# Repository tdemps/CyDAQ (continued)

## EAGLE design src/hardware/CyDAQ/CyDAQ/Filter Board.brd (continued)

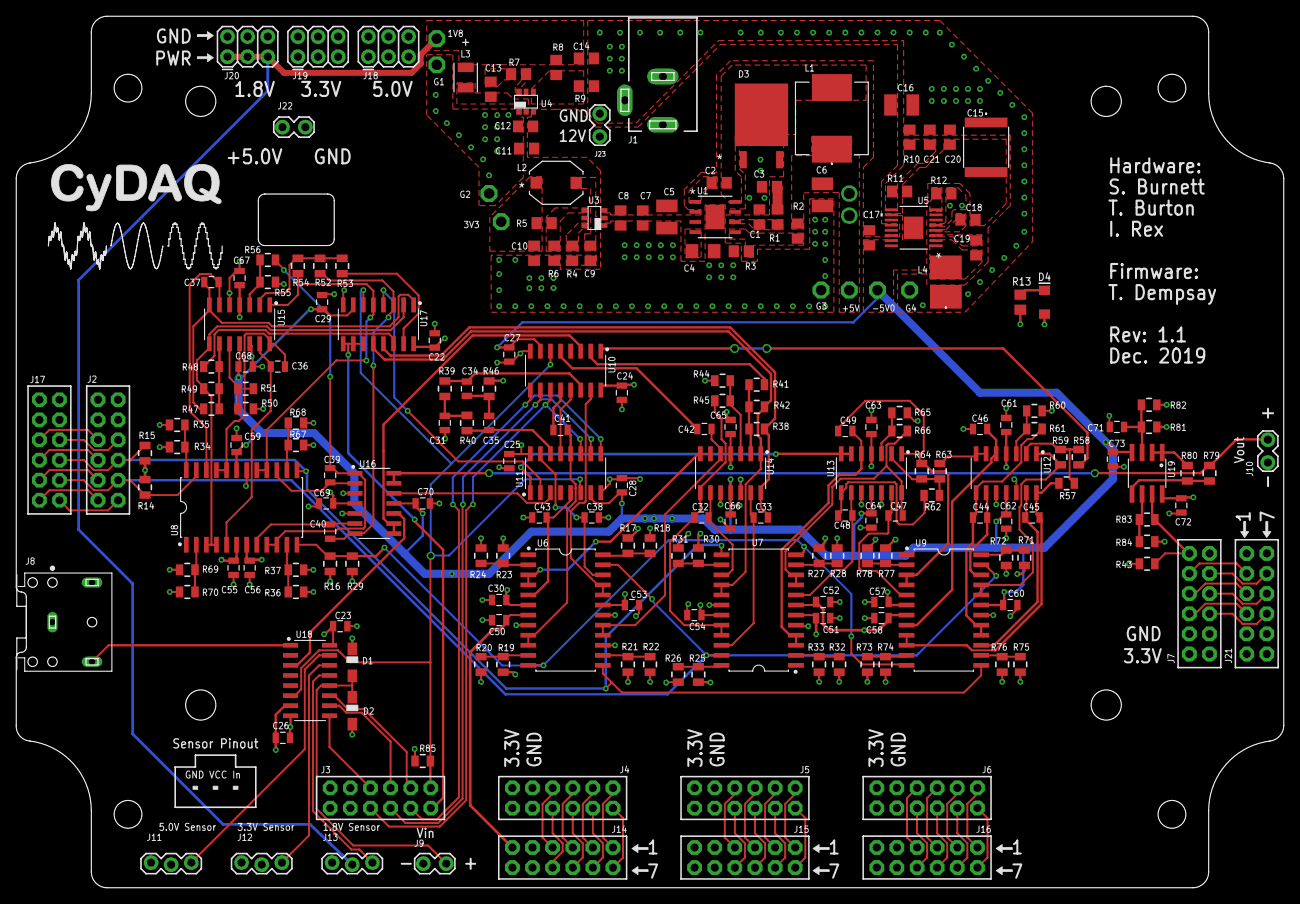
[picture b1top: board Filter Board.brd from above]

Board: 4 copper layers, 160.0 x 110.0 mm, 215 parts (0 on the bottom side), 160 nets.

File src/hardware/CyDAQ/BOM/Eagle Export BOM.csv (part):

"Part";"Value";"Device";"Package";"Description";"AVAILABILITY";"BOM";"CUI_PURCHASE_URL";"DESCRIPTION";"MANUFACTURER_PART_NUMBER";"MF";"MP";"MPN";"OC_FARNELL";"OC_NEWARK";"PACKAGE";"POPULARITY";"PRICE";"PROD_ID";"SPICEPREFIX";"TP_SIGNAL_NAME";"URL";"VALUE";"VENDOR";
"+5V";"TPPAD1-13";"TPPAD1-13";"P1-13";"Test pad";"";"";"";"";"";"";"";"";"";"";"";"12";"";"";"";"";"";"";"";
"-5V";"TPPAD1-13";"TPPAD1-13";"P1-13";"Test pad";"";"";"";"";"";"";"";"";"";"";"";"12";"";"";"";"";"";"";"";
"1V8";"TPPAD1-13";"TPPAD1-13";"P1-13";"Test pad";"";"";"";"";"";"";"";"";"";"";"";"12";"";"";"";"";"";"";"";
"3V3";"TPPAD1-13";"TPPAD1-13";"P1-13";"Test pad";"";"";"";"";"";"";"";"";"";"";"";"12";"";"";"";"";"";"";"";
"C1";"10pF";"C-USC0805";"C0805";"CAPACITOR, American symbol";"";"";"";"";"";"";"";"";"";"";"";"63";"";"";"C";"";"";"";"";
"C2";"100nF";"C-USC0805";"C0805";"CAPACITOR, American symbol";"";"";"";"";"";"";"";"";"";"";"";"63";"";"";"C";"";"";"";"";
"C3";"1.2nF";"C-USC0805";"C0805";"CAPACITOR, American symbol";"";"";"";"";"";"";"";"";"";"";"";"63";"";"";"C";"";"";"";"";
"C4";"8.2nF";"C-USC1206";"C1206";"CAPACITOR, American symbol";"";"";"";"";"";"";"";"";"";"";"";"24";"";"";"C";"";"";"";"";
"C5";"10uF";"C-USC1210";"C1210";"CAPACITOR, American symbol";"";"";"";"";"";"";"";"";"";"";"";"6";"";"";"C";"";"";"";"";
"C6";"47uF";"C-USC1210";"C1210";"CAPACITOR, American symbol";"";"";"";"";"";"";"";"";"";"";"";"6";"";"";"C";"";"";"";"";
"C7";"10uF";"C-USC0805";"C0805";"CAPACITOR, American symbol";"";"";"";"";"";"";"";"";"";"";"";"63";"";"";"C";"";"";"";"";
"C8";"100nF";"C-USC0805";"C0805";"CAPACITOR, American symbol";"";"";"";"";"";"";"";"";"";"";"";"63";"";"";"C";"";"";"";"";
"C9";"100nF";"C-USC0805";"C0805";"CAPACITOR, American symbol";"";"";"";"";"";"";"";"";"";"";"";"63";"";"";"C";"";"";"";"";
"C10";"22uF";"C-USC0805";"C0805";"CAPACITOR, American symbol";"";"";"";"";"";"";"";"";"";"";"";"63";"";"";"C";"";"";"";"";
"C11";"10uF";"C-USC0805";"C0805";"CAPACITOR, American symbol";"";"";"";"";"";"";"";"";"";"";"";"63";"";"";"C";"";"";"";"";
"C12";"100nF";"C-USC0805";"C0805";"CAPACITOR, American symbol";"";"";"";"";"";"";"";"";"";"";"";"63";"";"";"C";"";"";"";"";
"C13";"100nF";"C-USC0805";"C0805";"CAPACITOR, American symbol";"";"";"";"";"";"";"";"";"";"";"";"63";"";"";"C";"";"";"";"";
"C14";"22uF";"C-USC0805";"C0805";"CAPACITOR, American symbol";"";"";"";"";"";"";"";"";"";"";"";"63";"";"";"C";"";"";"";"";
"C15";"47uF";"CGA9N3X7R1_CGA9N3X7R1C476M230KB";"CGA9N3X7R1_CAP_5750";"";"";"";"";"";"CGA9N3X7R1C476M230KB";"";"";"";"";"";"";"";"";"";"";"";"";"";"TDK";
"C16";"22uF";"C-USC1210";"C1210";"CAPACITOR, American symbol";"";"";"";"";"";"";"";"";"";"";"";"6";"";"";"C";"";"";"";"";
"C17";"4.7uF";"C-USC0805";"C0805";"CAPACITOR, American symbol";"";"";"";"";"";"";"";"";"";"";"";"63";"";"";"C";"";"";"";"";
"C18";"2.2uF";"C-USC0805";"C0805";"CAPACITOR, American symbol";"";"";"";"";"";"";"";"";"";"";"";"63";"";"";"C";"";"";"";"";
"C19";"";"C-USC0805";"C0805";"CAPACITOR, American symbol";"";"";"";"";"";"";"";"";"";"";"";"63";"";"";"C";"";"";"";"";
"C20";"4.7uF";"C-USC0805";"C0805";"CAPACITOR, American symbol";"";"";"";"";"";"";"";"";"";"";"";"63";"";"";"C";"";"";"";"";
"C21";"33pF";"C-USC0805";"C0805";"CAPACITOR, American symbol";"";"";"";"";"";"";"";"";"";"";"";"63";"";"";"C";"";"";"";"";
"C22";"0.1uF";"NON_POL_0805/2012";"0805_H0.75";"";"";"";"";"";"";"";"";"";"";"";"";"";"";"";"";"";"";"";"";
"C23";"0.1uF";"NON_POL_0805/2012";"0805_H0.75";"";"";"";"";"";"";"";"";"";"";"";"";"";"";"";"";"";"";"";"";
"C24";"0.1uF";"NON_POL_0805/2012";"0805_H0.75";"";"";"";"";"";"";"";"";"";"";"";"";"";"";"";"";"";"";"";"";
"C25";"0.1uF";"NON_POL_0805/2012";"0805_H0.75";"";"";"";"";"";"";"";"";"";"";"";"";"";"";"";"";"";"";"";"";
"C26";"0.1uF";"NON_POL_0805/2012";"0805_H0.75";"";"";"";"";"";"";"";"";"";"";"";"";"";"";"";"";"";"";"";"";
"C27";"0.1uF";"NON_POL_0805/2012";"0805_H0.75";"";"";"";"";"";"";"";"";"";"";"";"";"";"";"";"";"";"";"";"";
"C28";"0.1uF";"NON_POL_0805/2012";"0805_H0.75";"";"";"";"";"";"";"";"";"";"";"";"";"";"";"";"";"";"";"";"";
"C29";"0.1uF";"NON_POL_0805/2012";"0805_H0.75";"";"";"";"";"";"";"";"";"";"";"";"";"";"";"";"";"";"";"";"";
"C30";"0.1uF";"NON_POL_0805/2012";"0805_H0.75";"";"";"";"";"";"";"";"";"";"";"";"";"";"";"";"";"";"";"";"";
"C31";"10uF";"NON_POL_0805/2012";"0805_H0.75";"";"";"";"";"";"";"";"";"";"";"";"";"";"";"";"";"";"";"";"";
"C32";"10nF";"NON_POL_0805/2012";"0805_H0.75";"";"";"";"";"";"";"";"";"";"";"";"";"";"";"";"";"";"";"";"";
"C33";"10nF";"NON_POL_0805/2012";"0805_H0.75";"";"";"";"";"";"";"";"";"";"";"";"";"";"";"";"";"";"";"";"";
"C34";"5.6uF";"NON_POL_0805/2012";"0805_H0.75";"";"";"";"";"";"";"";"";"";"";"";"";"";"";"";"";"";"";"";"";
"C35";"5.6uF";"NON_POL_0805/2012";"0805_H0.75";"";"";"";"";"";"";"";"";"";"";"";"";"";"";"";"";"";"";"";"";
"C36";"10nF";"NON_POL_0805/2012";"0805_H0.75";"";"";"";"";"";"";"";"";"";"";"";"";"";"";"";"";"";"";"";"";
"C37";"10nF";"NON_POL_0805/2012";"0805_H0.75";"";"";"";"";"";"";"";"";"";"";"";"";"";"";"";"";"";"";"";"";
"C38";"10nF";"NON_POL_0805/2012";"0805_H0.75";"";"";"";"";"";"";"";"";"";"";"";"";"";"";"";"";"";"";"";"";
"C39";"10nF";"NON_POL_0805/2012";"0805_H0.75";"";"";"";"";"";"";"";"";"";"";"";"";"";"";"";"";"";"";"";"";
"C40";"10nF";"NON_POL_0805/2012";"0805_H0.75";"";"";"";"";"";"";"";"";"";"";"";"";"";"";"";"";"";"";"";"";
"C41";"10nF";"NON_POL_0805/2012";"0805_H0.75";"";"";"";"";"";"";"";"";"";"";"";"";"";"";"";"";"";"";"";"";
"C42";"10nF";"NON_POL_0805/2012";"0805_H0.75";"";"";"";"";"";"";"";"";"";"";"";"";"";"";"";"";"";"";"";"";
"C43";"10nF";"NON_POL_0805/2012";"0805_H0.75";"";"";"";"";"";"";"";"";"";"";"";"";"";"";"";"";"";"";"";"";
"C44";"10nF";"NON_POL_0805/2012";"0805_H0.75";"";"";"";"";"";"";"";"";"";"";"";"";"";"";"";"";"";"";"";"";
"C45";"10nF";"NON_POL_0805/2012";"0805_H0.75";"";"";"";"";"";"";"";"";"";"";"";"";"";"";"";"";"";"";"";"";
"C46";"10nF";"NON_POL_0805/2012";"0805_H0.75";"";"";"";"";"";"";"";"";"";"";"";"";"";"";"";"";"";"";"";"";
"C47";"10nF";"NON_POL_0805/2012";"0805_H0.75";"";"";"";"";"";"";"";"";"";"";"";"";"";"";"";"";"";"";"";"";
"C48";"10nF";"NON_POL_0805/2012";"0805_H0.75";"";"";"";"";"";"";"";"";"";"";"";"";"";"";"";"";"";"";"";"";
"C49";"10nF";"NON_POL_0805/2012";"0805_H0.75";"";"";"";"";"";"";"";"";"";"";"";"";"";"";"";"";"";"";"";"";
"C50";"0.1uF";"NON_POL_0805/2012";"0805_H0.75";"";"";"";"";"";"";"";"";"";"";"";"";"";"";"";"";"";"";"";"";
"C51";"0.1uF";"NON_POL_0805/2012";"0805_H0.75";"";"";"";"";"";"";"";"";"";"";"";"";"";"";"";"";"";"";"";"";
"C52";"0.1uF";"NON_POL_0805/2012";"0805_H0.75";"";"";"";"";"";"";"";"";"";"";"";"";"";"";"";"";"";"";"";"";
"C53";"0.1uF";"NON_POL_0805/2012";"0805_H0.75";"";"";"";"";"";"";"";"";"";"";"";"";"";"";"";"";"";"";"";"";
"C54";"0.1uF";"NON_POL_0805/2012";"0805_H0.75";"";"";"";"";"";"";"";"";"";"";"";"";"";"";"";"";"";"";"";"";
"C55";"0.1uF";"NON_POL_0805/2012";"0805_H0.75";"";"";"";"";"";"";"";"";"";"";"";"";"";"";"";"";"";"";"";"";
"C56";"0.1uF";"NON_POL_0805/2012";"0805_H0.75";"";"";"";"";"";"";"";"";"";"";"";"";"";"";"";"";"";"";"";"";
"C57";"0.1uF";"NON_POL_0805/2012";"0805_H0.75";"";"";"";"";"";"";"";"";"";"";"";"";"";"";"";"";"";"";"";"";
"C58";"0.1uF";"NON_POL_0805/2012";"0805_H0.75";"";"";"";"";"";"";"";"";"";"";"";"";"";"";"";"";"";"";"";"";
"C59";"0.1uF";"NON_POL_0805/2012";"0805_H0.75";"";"";"";"";"";"";"";"";"";"";"";"";"";"";"";"";"";"";"";"";
"C60";"0.1uF";"NON_POL_0805/2012";"0805_H0.75";"";"";"";"";"";"";"";"";"";"";"";"";"";"";"";"";"";"";"";"";
"C61";"0.1uF";"NON_POL_0805/2012";"0805_H0.75";"";"";"";"";"";"";"";"";"";"";"";"";"";"";"";"";"";"";"";"";
"C62";"0.1uF";"NON_POL_0805/2012";"0805_H0.75";"";"";"";"";"";"";"";"";"";"";"";"";"";"";"";"";"";"";"";"";
"C63";"0.1uF";"NON_POL_0805/2012";"0805_H0.75";"";"";"";"";"";"";"";"";"";"";"";"";"";"";"";"";"";"";"";"";
"C64";"0.1uF";"NON_POL_0805/2012";"0805_H0.75";"";"";"";"";"";"";"";"";"";"";"";"";"";"";"";"";"";"";"";"";
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
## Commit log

2019-10-30 -Initial commit with Zybo firmware, old design files, old labs, and misc documentation
    -All old source work on cyDAQ is under /Archive/
    -Documentation folder contains relevant lab files, datasheets, etc.
2019-10-30 Pushing to Hardware branch
2019-10-30 Added base CyDAQ Altium project
2019-10-31 Adding Documentation to lab dev branch
2019-10-31 Adding Fourier Matlab
2019-10-31 New answer key for Fourier Labs and First Draft of Fourier Lab
2019-11-01 -firmware branch
2019-11-01 Initial upload
2019-11-07 Simplified things and streamlined it with hints so students aren't as lost in the process.
2019-11-11 Edited the Fourier Lab.
2019-11-12 -Merged XADC and I2C work into full_firmware project
    -Fixed XADC interrupt function to only be called when sequence is finished
    -Tested XADC (very preliminary)
2019-11-15 Added EAGLE design files at start of routing stage
2019-11-15 Placed components and started routing
2019-11-18 Continued routing.
2019-11-19 -Added comm test to main (Loopback for host)
    -Added button GPIO access to design
    -More XADC testing
    -Changed default AUX14 setting to unipolar
2019-11-19 Adding HW Datasheets
2019-11-19 Finished routing BP filter
2019-11-19 Rearranged some components for clarity
2019-11-20 Continued routing ~ 80% done
2019-11-20 Added some more traces!
2019-11-20 Used Gateswap magic to clean up some routing
2019-11-20 -changes
2019-11-20 Finished routing main filter area
2019-11-21 Finished most routing. Need to do -5v rail
2019-11-21 Fixed PMOD location
2019-11-21 Finished routing and made mechanical adjustments
2019-11-22 Added LED and fixed mounting holes
2019-11-22 Cleaned up frames
2019-11-22 Changed backup files
2019-11-22 Added silkscreen
2019-11-22 Made some final adjustments and added production files
2019-11-22 Adding Sam's BOM
2019-11-23 Updated silkscreen and uploaded board layout PDF
2019-11-23 Uploaded searchable schematic PDFs
2019-11-26 Adjusted notch filter values and uploaded BOM
2019-12-02 Added latest BOM
2019-12-02 Added marked layout PDF
2019-12-02 Updated TODO
2019-12-03 -encapsuled all filter definitions in filter library
    -redesigned mux and filter libraries to use main filter enum
    -many other improvements
2019-12-04 Fixed output MUX mapping
2019-12-05 Started fixing pinout on MUXs
2019-12-05 Finished rerouting fixed pinout
2019-12-09 -Added filter test in main.c
    -Added blank fsbl project to create BOOT.BIN for sdcard
    -Moved X9258 address macros to filter.h
    -Corrected some mux configs
    -Revised mux_driver to use PLL GPIO block instead of PS object
    -Rerouted filter and mux select pins to JE for Zybo
2019-12-09 Fixed button filter select on filter test
2019-12-09 Adding Sam's redesgined PMICs
2019-12-10 Modified board outline and updated silkscreen
2019-12-10 -Started working on timer based xadc
    -Added button blocking function
2019-12-10 Front end 2.0 initial commit
2019-12-10 Fixed Zybo mounting hole location
2019-12-12 -And the lord said let there be comments
    -Removal of some dusty commented code
    -Moved some definitions to their appropiate header files
2019-12-13 -Added debug flag support to more print statements
    -Added ping command
    -Added fetch command
    -Reworked sampling loop to decrease instructions between sample checks (less dropped samples)
    -Increased sample buffer size to 3000000
2019-12-16 -Changes to test program
2019-12-19 Fixed op-amp letter mapping library.
2019-12-24 Changed silkscreen and minor mechancial changes
2019-12-27 Adding CyDAQ testing results and BOM with costs
2020-01-06 parsing and saving the data
2020-01-11 Adjusted C3 Silkscreen and added 3D renders
2020-01-11 Added step file for finished enclosure
2020-01-13 updated communication with zybo
2020-01-13 Seperated ctrl_comm file into 2 seperate files
2020-01-13 -Created global variable with currently selected filter
    -Changed sample data to be sent using uartfunction (less overhead than xil_printf)
    -corner set command no longer requires comma or filter number from gui
2020-01-13 Added SD card slot to enclosure Model
2020-01-14 Added SD card slot to enclosure
2020-01-14 Adding Sam's PMIC Webench Designs
2020-01-15 corner freq update
2020-01-17 Fixed SD card loction on Enclosure
2020-01-17 -Converted standalone tests to take uart input
    -Added delay in sending samples to avoid buffer filling on gui side
2020-01-21 Added PDFs for board and schematic
2020-01-21 Added board layout PDF for DNU parts
2020-01-21 Added enclosure Drawing
2020-01-21 Adding Enclosure Step file and drawing
2020-01-21 -Added logic to resend sample data if FIFO is full
2020-01-21 -Tweaked sample receive function
    -Moved some gui globals to be object variables
    -Put csv export into try except statement to catch errors
2020-01-22 -remove check connection in serial
2020-01-22 -removed cache files
    -edited git ignore
2020-01-24 Updated J18:20 in BOM and added filter test spreadsheet
2020-01-27 Fixed uart protocol when transferring samples
2020-01-27 fixed sample transfer reading, optimized date processing to minimize time delay
2020-01-27 - added corner freq to send_parammeters function
    -pop up box when zybo is not initially connected
2020-01-28 -Added checks for several input options
    -Fixed config update logic
2020-01-28 -Merge fix
2020-01-29 -Added sequencer setting macro to xadc.h
    -Converted xadc config to single channel sampling (aux14)
    -Added initialization checks to pot,mux lib functions
    -Removed multiplier feature from incr/decr command in filtertest (buggy)
    -v0.9, system testing with GUI is going well.
2020-01-29 -Renamed enum classes to be shorter and more readable
    -Removed unneeded imports and converted several methods to standalone functions
    -Fixed filter command sending function
    -Added .mat export option for sample data (BETA)
    -Added sample rate max and min variables instead of hardcoded values
    -open instructions function uses current directory instead of hardcoded absolute one
    -Added com port value check in open function to prevent unhandled exceptions
2020-01-29 -fixed xadc init recursion bug
2020-01-30 -Added voltage vector to .mat export
    -added a few else statements to eliminate unhandled cases in config
    -Added another com port check before starting sampling
2020-01-30 -Fixed input command execution
2020-01-30 -Added requirements.txt for package needs
    -Added spec file for use with pyinstaller
    -Modified .gitignore to exclude pyinstaller build directories
    -Added exported exe in dist directory
    -Added instructions file (IN PROGRESS)
2020-01-31 - sample button on main page
    - sample page is now hidden
2020-02-03 Organized testing folder
2020-02-03 -Fixed a few bugs from moving the sample button
    -Recompiled exe with new GUI
    -Fixed cmd in instructions.txt
2020-02-06 Uploaded CyDAQ renders
2020-02-06 Restored PDF folder
2020-02-06 Updated render
2020-02-06 Updated render coloring
2020-02-06 Added render of enclosure
2020-02-10 -Changed several functions to use standard Xilinx return values (XStatus, etc.)
    -Added AXI Timer datasheet
    -Added more funtion documentation
2020-02-12 -Added sd_config library to support loading filter board settings from sd card file.
    Instructions on these are in src/firmware/423 Config files/README.txt
    -Added minimal JSON parsing C library to firmware project
    -Xilffs library added to firmware bsp for sd card file system reading
2020-02-13 Added mechanical BOM
2020-02-13 -Added firmware specific readme.md (in progress)
2020-02-14 Added rubber feet to BOM
2020-03-02 -Minor changes to test program
2020-03-07 -Fixed sd card loading of config file
    -Program now continues running program after loading sd config
2022-06-22 Bump numpy from 1.16.4 to 1.22.0 in /src/font_end_2.0
    Bumps [numpy](https://github.com/numpy/numpy) from 1.16.4 to 1.22.0.
    - [Release notes](https://github.com/numpy/numpy/releases)
    - [Changelog](https://github.com/numpy/numpy/blob/main/doc/HOWTO_RELEASE.rst)
    - [Commits](https://github.com/numpy/numpy/compare/v1.16.4...v1.22.0)
    ---
    updated-dependencies:
2023-07-06 Bump scipy from 1.3.0 to 1.10.0 in /src/font_end_2.0
    Bumps [scipy](https://github.com/scipy/scipy) from 1.3.0 to 1.10.0.
    - [Release notes](https://github.com/scipy/scipy/releases)
    - [Commits](https://github.com/scipy/scipy/compare/v1.3.0...v1.10.0)
    ---
    updated-dependencies:
    - dependency-name: scipy
